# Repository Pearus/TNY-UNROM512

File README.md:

# TNY-UNROM512

This is a custom UNROM512 board for the TinyTendo handheld console by <a href="https://github.com/Redherring32">Redherring32</a>. This board replicates <a href="https://www.nesdev.org/wiki/UNROM_512">standard UNROM 512 NES boards</a>. 

Since these boards use the 39SF040 for the PRG ROM, you should use FamiROM or some other utility to duplicate the ROM files to completely fill up the entire space on the Flash chip if necessary.

# TNY-UNROM512 Board Characteristics

- Thickness: 1.6 mm
- Surface Finish: ENIG
- Chamfered edges (45°)

# How to Use This Board

*Note: Do not solder U1 to the board before programming it.*

UNROM512 games require every component on the board.

The solder jumpers must be bridged according to the NES game you program.

## Flashing the Game

Prepare the ROM using FamiROM or other similar program, ensuring the entire 4Mbit space is filled for the PRG component. You then need to program the 39SF040 before soldering it to the board. I use a <a href="https://www.embeddedcomputers.net/products/FlashcatUSB_XPORT/">FlashCat</a> with a <a href="https://www.embeddedcomputers.net/products/ParallelAdapters/">TSOP-32 adapter (Type B)</a> to achieve this.

# Bill of Materials

Capacitors should be at least 16V rated.

| Reference Designator  | Part Number/Value | Footprint  |
| ------------- | ------------- | ------------- |
| C1  | 22 uF | 1206  |
| C2-C7  | 0.1 uF | 0603  |
| U1  | <a href="https://www.mouser.com/ProductDetail/Microchip-Technology/SST39SF040-70-4C-WHE?qs=Oo69DRhzroe%2FJKrgAmUE5Q%3D%3D">39SF040</a>  | TSOP32 (14mm) |
| U2  | <a href="https://www.mouser.com/ProductDetail/Alliance-Memory/AS6C6264-55STCN?qs=LD2UibpCYJonFY2RVods7g%3D%3D">AS6C6264</a> or <a href="https://www.mouser.com/ProductDetail/870-IS61C64AL-10TLI">IS61C64AL-10TLI</a>  | TSOP28 |
| U3  | <a href="https://www.mouser.com/en/ProductDetail/Texas-Instruments/SN74HC32PWR?qs=ZA235jQDfbp291NIbGpFPA%3D%3D&srsltid=AfmBOoqr3tJiAp05AKdq0nheTTSW8kXJ8rZ0H6d5TP8TUHp8teFPOZYZ">SN74HC32PWR</a>              | TSSOP14 |
| U4  | <a href="https://www.mouser.com/en/ProductDetail/Texas-Instruments/SN74HC32PWR?qs=ZA235jQDfbp291NIbGpFPA%3D%3D&srsltid=AfmBOoqr3tJiAp05AKdq0nheTTSW8kXJ8rZ0H6d5TP8TUHp8teFPOZYZ">SN74HC32PWR</a>              | TSSOP14 |
| U5  | <a href="https://www.mouser.com/en/ProductDetail/Texas-Instruments/SN74HC139PWR?qs=%252BWCn1GN4mVzsIRktqzW%252B6w%3D%3D">SN74HC139PWR</a>              | TSSOP16 |
| U6  | <a href="https://www.mouser.com/en/ProductDetail/Texas-Instruments/SN74HC377DWR?qs=VolsR0DjNPqmUtsQyZQkhw%3D%3D">SN74HC377DWR</a>              | SOIC20 |

# Revision History

## v1.0

- Initial version

## License
<br />This work is licensed under a <a rel="license" href="http://creativecommons.org/licenses/by-sa/4.0/">Creative Commons Attribution-ShareAlike 4.0 International License</a>. You are able to copy and redistribute the material in any medium or format, as well as remix, transform, or build upon the material for any purpose (even commercial) - but you **must** give appropriate credit, provide a link to the license, and indicate if any changes were made.

## Credits

*Redherring32* - Creating the TinyTendo project.

*BucketMouse* - Original MMC3 and NROM cartridge designs for TinyTendo which this is an extension of.

*NESDev* - Wiki was heavily referenced as part of writing the schematic and troubleshooting.

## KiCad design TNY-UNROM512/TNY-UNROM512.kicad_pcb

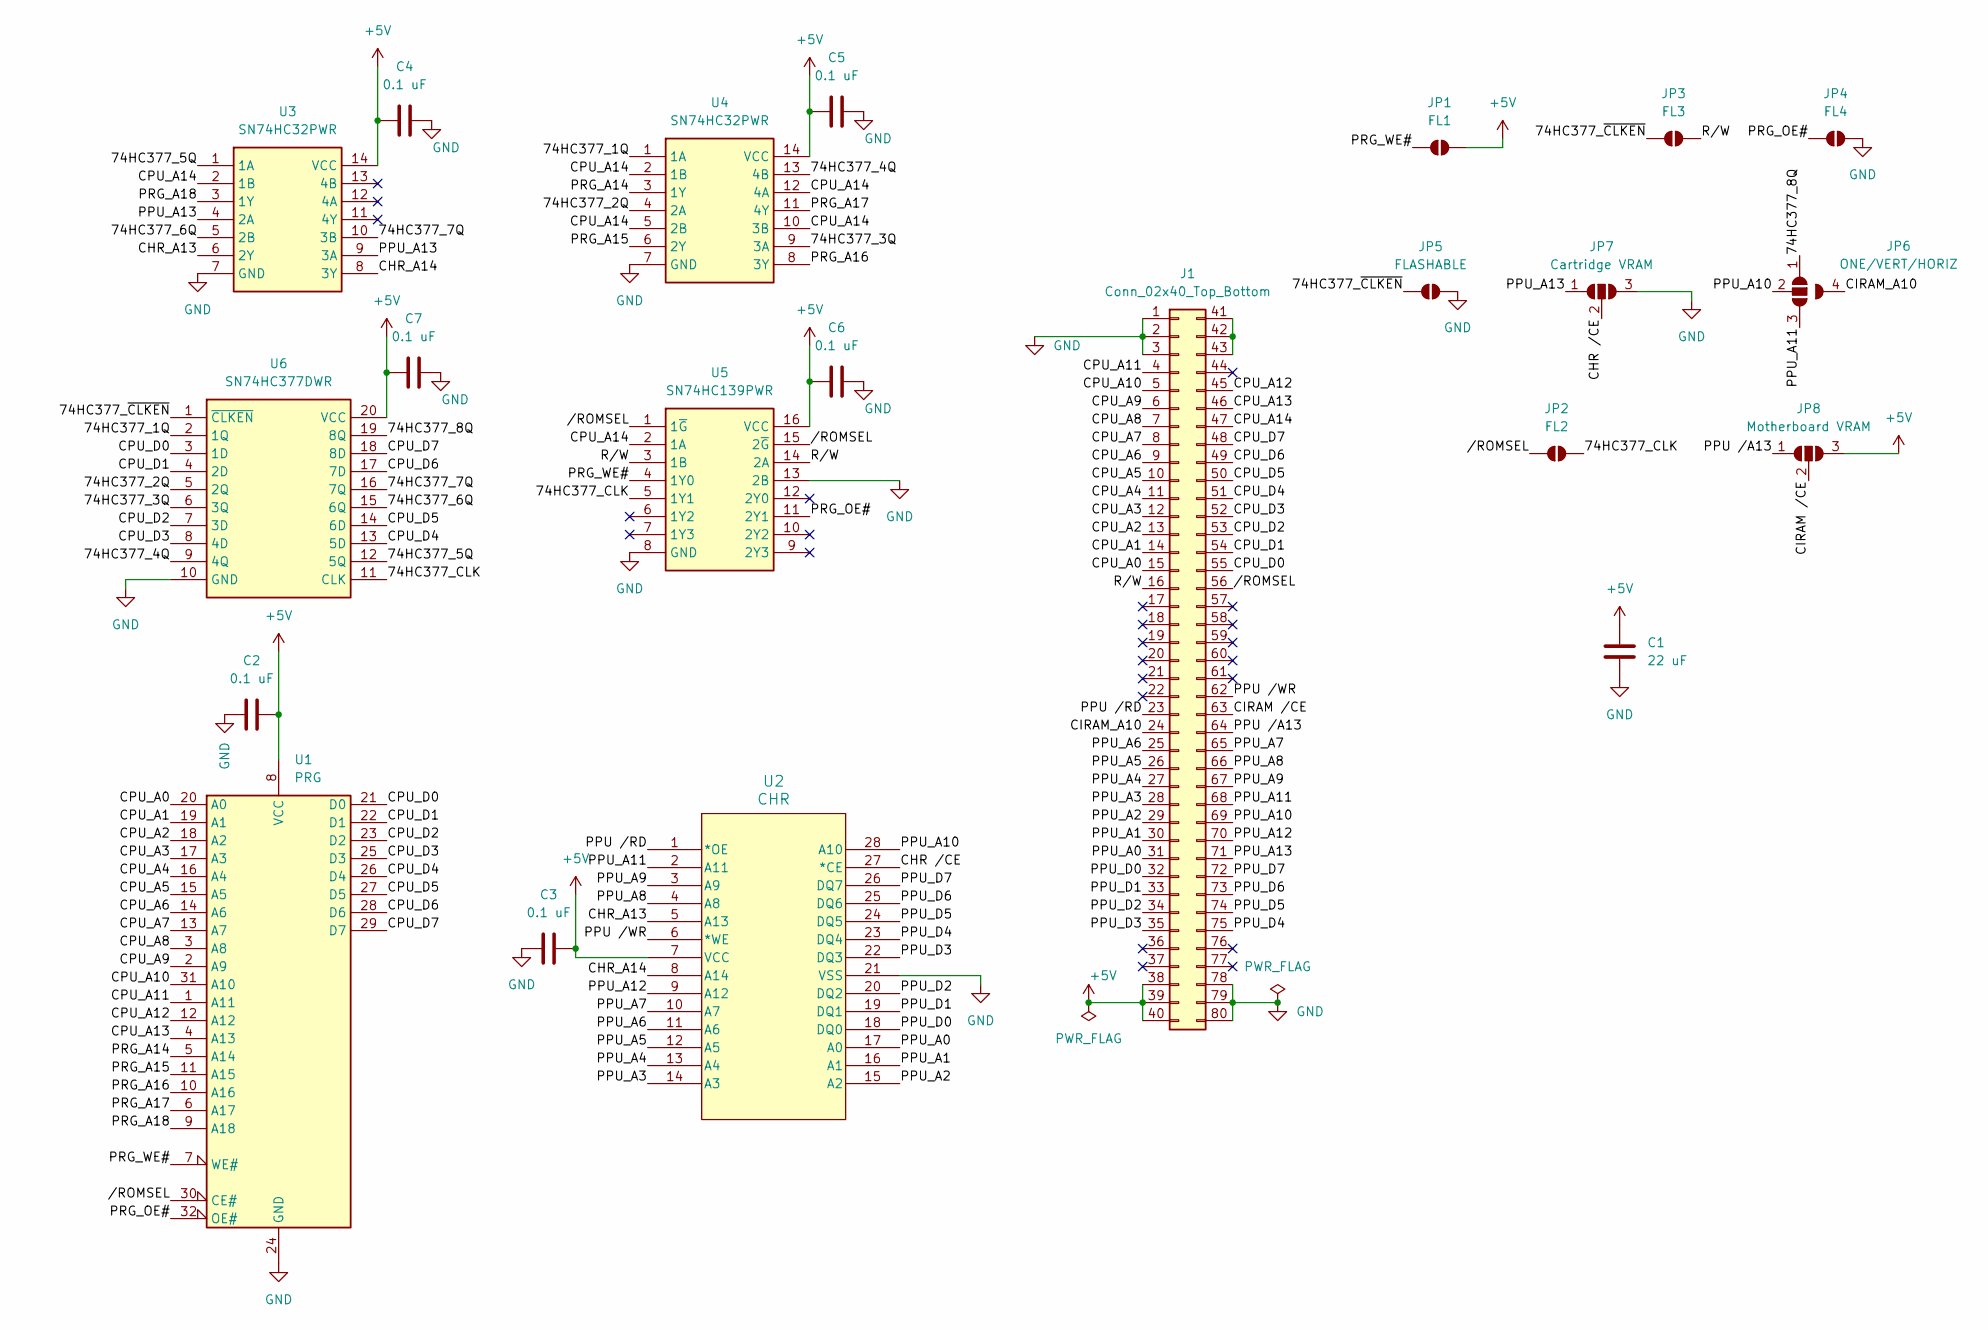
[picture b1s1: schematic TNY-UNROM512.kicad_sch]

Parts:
C1: 22 uF; C_1206_3216Metric
C2, C3, C4, C5, C6, C7: 0.1 uF; C_0603_1608Metric
J1: Conn_02x40_Top_Bottom; TNY-UNROM512 Edge Connector
JP1: FL1; Jumper
JP2: FL2; Jumper
JP3: FL3; Jumper
JP4: FL4; Jumper
JP5: FLASHABLE; Jumper
JP6: ONE/VERT/HORIZ; CIRAM_A10 Jumper
JP7: Cartridge VRAM; Screen Jumper
JP8: Motherboard VRAM; Screen Jumper
U1: PRG; TSOP-32
U2: CHR; TSOP-28
U3, U4: SN74HC32PWR; Mouser Part Number 595-SN74HC32PWR
U5: SN74HC139PWR; Mouser Part Number 595-SN74HC139PWR
U6: SN74HC377DWR; Mouser Part Number 595-SN74HC377DWR

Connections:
+5V: C1.1, C2.2, C3.1, C4.2, C5.2, C6.2, C7.2, J1.38, J1.39, J1.40, JP1.2 (B), JP8.3 (B), U1.8 (VCC), U2.7 (VCC), U3.14 (VCC), U4.14 (VCC), U5.16 (VCC), U6.20 (VCC)
/74HC377_1Q: U4.1 (1A), U6.2 (1Q)
/74HC377_2Q: U4.4 (2A), U6.5 (2Q)
/74HC377_3Q: U4.9 (3A), U6.6 (3Q)
/74HC377_4Q: U4.13 (4B), U6.9 (4Q)
/74HC377_5Q: U3.1 (1A), U6.12 (5Q)
/74HC377_6Q: U3.5 (2B), U6.15 (6Q)
/74HC377_7Q: U3.10 (3B), U6.16 (7Q)
/74HC377_8Q: JP6.1 (A), U6.19 (8Q)
/74HC377_CLK: JP2.2 (B), U5.5 (1Y1), U6.11 (CLK)
/74HC377_~CLKEN: JP3.1 (A), JP5.1 (A), U6.1 (~CLKEN)
/CHR /CE: JP7.2 (C), U2.27 (*CE)
/CHR_A13: U2.5 (A13), U3.6 (2Y)
/CHR_A14: U2.8 (A14), U3.8 (3Y)
/CIRAM /CE: J1.63, JP8.2 (C)
/CIRAM_A10: J1.24, JP6.4 (A)
/CPU_A0: J1.15, U1.20 (A0)
/CPU_A1: J1.14, U1.19 (A1)
/CPU_A2: J1.13, U1.18 (A2)
/CPU_A3: J1.12, U1.17 (A3)
/CPU_A4: J1.11, U1.16 (A4)
/CPU_A5: J1.10, U1.15 (A5)
/CPU_A6: J1.9, U1.14 (A6)
/CPU_A7: J1.8, U1.13 (A7)
/CPU_A8: J1.7, U1.3 (A8)
/CPU_A9: J1.6, U1.2 (A9)
/CPU_A10: J1.5, U1.31 (A10)
/CPU_A11: J1.4, U1.1 (A11)
/CPU_A12: J1.45, U1.12 (A12)
/CPU_A13: J1.46, U1.4 (A13)
/CPU_A14: J1.47, U3.2 (1B), U4.2 (1B), U4.5 (2B), U4.10 (3B), U4.12 (4A), U5.2 (1A)
/CPU_D0: J1.55, U1.21 (D0), U6.3 (1D)
/CPU_D1: J1.54, U1.22 (D1), U6.4 (2D)
/CPU_D2: J1.53, U1.23 (D2), U6.7 (3D)
/CPU_D3: J1.52, U1.25 (D3), U6.8 (4D)
/CPU_D4: J1.51, U1.26 (D4), U6.13 (5D)
/CPU_D5: J1.50, U1.27 (D5), U6.14 (6D)
/CPU_D6: J1.49, U1.28 (D6), U6.17 (7D)
/CPU_D7: J1.48, U1.29 (D7), U6.18 (8D)
/PPU /A13: J1.64, JP8.1 (A)
/PPU /RD: J1.23, U2.1 (*OE)
/PPU /WR: J1.62, U2.6 (*WE)
/PPU_A0: J1.31, U2.17 (A0)
/PPU_A1: J1.30, U2.16 (A1)
/PPU_A2: J1.29, U2.15 (A2)
/PPU_A3: J1.28, U2.14 (A3)
/PPU_A4: J1.27, U2.13 (A4)
/PPU_A5: J1.26, U2.12 (A5)
/PPU_A6: J1.25, U2.11 (A6)
/PPU_A7: J1.65, U2.10 (A7)
/PPU_A8: J1.66, U2.4 (A8)
/PPU_A9: J1.67, U2.3 (A9)
/PPU_A10: J1.69, JP6.2 (C), U2.28 (A10)
/PPU_A11: J1.68, JP6.3 (B), U2.2 (A11)
/PPU_A12: J1.70, U2.9 (A12)
/PPU_A13: J1.71, JP7.1 (A), U3.4 (2A), U3.9 (3A)
/PPU_D0: J1.32, U2.18 (DQ0)
/PPU_D1: J1.33, U2.19 (DQ1)
/PPU_D2: J1.34, U2.20 (DQ2)
/PPU_D3: J1.35, U2.22 (DQ3)
/PPU_D4: J1.75, U2.23 (DQ4)
/PPU_D5: J1.74, U2.24 (DQ5)
/PPU_D6: J1.73, U2.25 (DQ6)
/PPU_D7: J1.72, U2.26 (DQ7)
/PRG_A14: U1.5 (A14), U4.3 (1Y)
/PRG_A15: U1.11 (A15), U4.6 (2Y)
/PRG_A16: U1.10 (A16), U4.8 (3Y)
/PRG_A17: U1.6 (A17), U4.11 (4Y)
/PRG_A18: U1.9 (A18), U3.3 (1Y)
/PRG_OE#: JP4.1 (A), U1.32 (OE#), U5.11 (2Y1)
/PRG_WE#: JP1.1 (A), U1.7 (WE#), U5.4 (1Y0)
/R/W: J1.16, JP3.2 (B), U5.3 (1B), U5.14 (2A)
//ROMSEL: J1.56, JP2.1 (A), U1.30 (CE#), U5.1 (1~G), U5.15 (2~G)
GND: C1.2, C2.1, C3.2, C4.1, C5.1, C6.1, C7.1, J1.1, J1.2, J1.3, J1.78, J1.79, J1.80, JP4.2 (B), JP5.2 (B), JP7.3 (B), U1.24 (GND), U2.21 (VSS), U3.7 (GND), U4.7 (GND), U5.8 (GND), U5.13 (2B), U6.10 (GND)
unnamed: J1.41, J1.42, J1.43

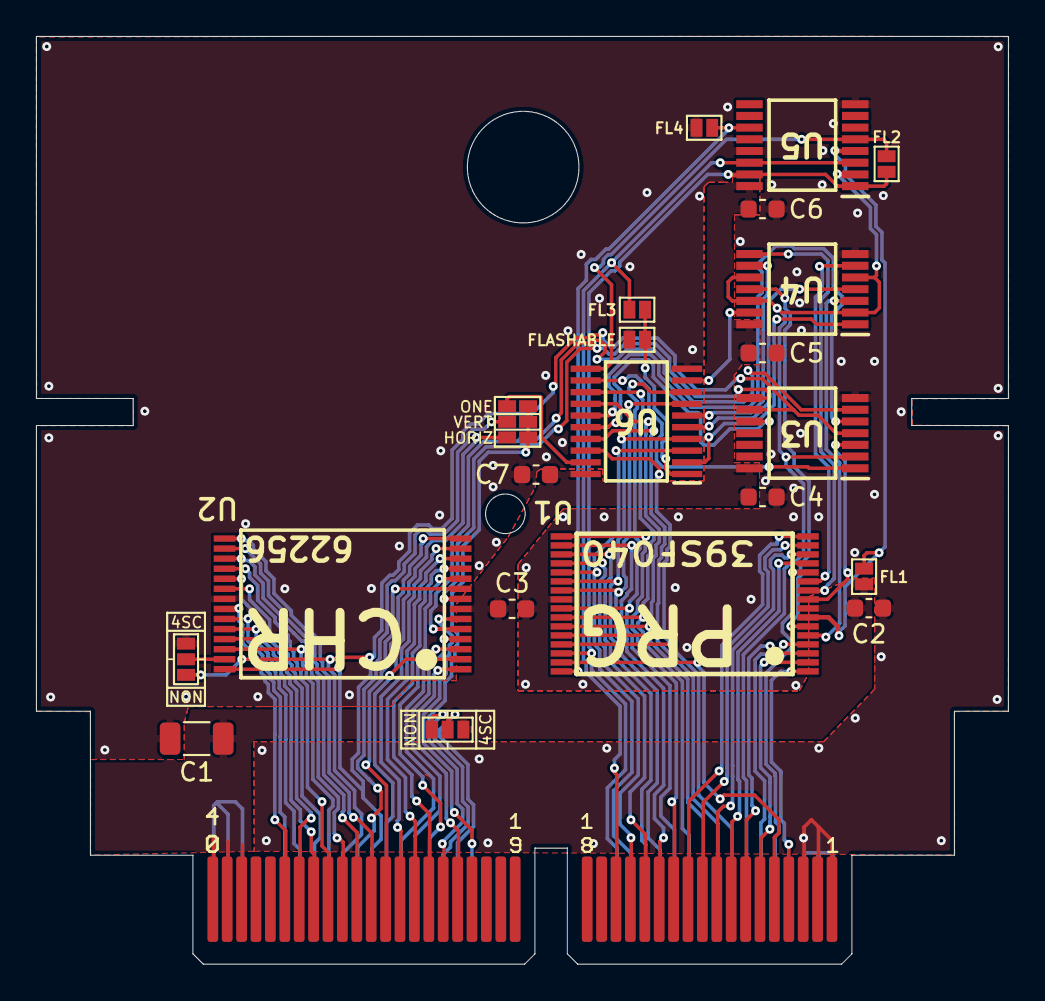
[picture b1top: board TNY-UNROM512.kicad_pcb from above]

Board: 2 copper layers, 54.0 x 51.5 mm, 22 parts (0 on the bottom side), 75 nets.
